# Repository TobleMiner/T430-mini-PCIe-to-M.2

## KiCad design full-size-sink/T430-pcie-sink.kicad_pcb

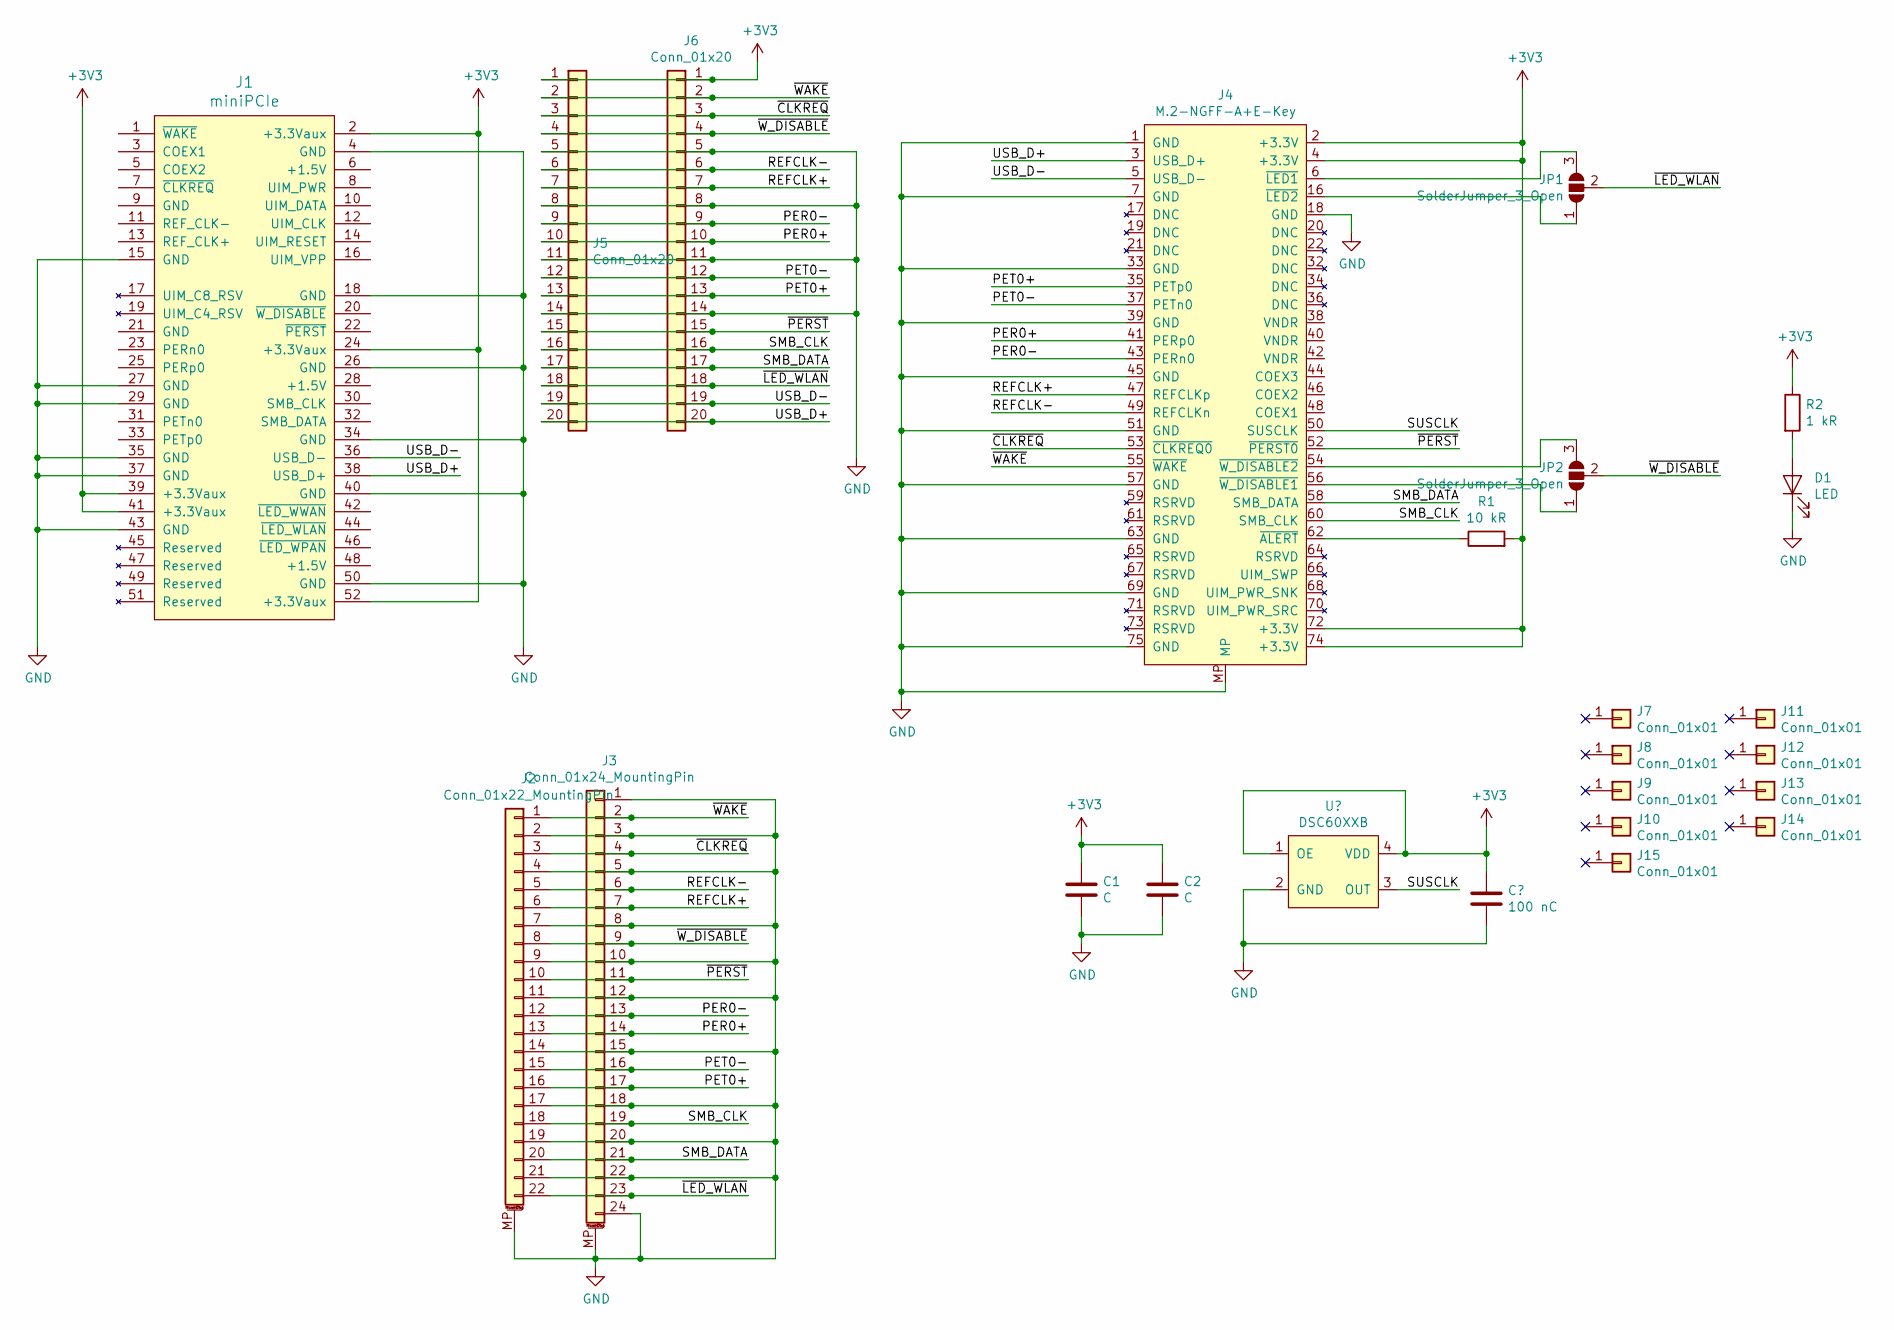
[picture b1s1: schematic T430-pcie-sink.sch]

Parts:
C1, C2: C; C_0805_2012Metric_Pad1.15x1.40mm_HandSolder
D1: LED; LED_0805_2012Metric_Castellated
J1: miniPCIe; mini-PCIe_F1_Full
J2: Conn_01x22_MountingPin; Molex-Easy-On-54548-2271-P0.5
J3: Conn_01x24_MountingPin; Molex-Easy-On-54548-2471-P0.5
J4: M.2-NGFF-A+E-Key; MDTXXXXXX001
J5: Conn_01x20; solder-20p-P1.0
J6: Conn_01x20; castellated-20p-P1.0
J7, J8, J9, J10, J11, J12, J13, J14: Conn_01x01; Pad-2.5x2.5
J15: Conn_01x01; screw-stud
JP1, JP2: SolderJumper_3_Open; SolderJumper-3_P1.3mm_Open_Pad1.0x1.5mm
R1: 10 kR; R_0805_2012Metric_Pad1.15x1.40mm_HandSolder
R2: 1 kR; R_0805_2012Metric_Pad1.15x1.40mm_HandSolder

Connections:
+3V3: C1.1, C2.1, J1.2 (+3.3Vaux), J1.24 (+3.3Vaux), J1.39 (+3.3Vaux), J1.41 (+3.3Vaux), J1.52 (+3.3Vaux), J4.2 (+3.3V), J4.4 (+3.3V), J4.72 (+3.3V), J4.74 (+3.3V), J5.1, J6.1, R1.2, R2.1; also elsewhere on the board
/PER0+: J2.13, J3.14, J4.41 (PERp0), J5.10, J6.10
/PER0-: J2.12, J3.13, J4.43 (PERn0), J5.9, J6.9
/PET0+: J2.16, J3.17, J4.35 (PETp0), J5.13, J6.13
/PET0-: J2.15, J3.16, J4.37 (PETn0), J5.12, J6.12
/REFCLK+: J2.6, J3.7, J4.47 (REFCLKp), J5.7, J6.7
/REFCLK-: J2.5, J3.6, J4.49 (REFCLKn), J5.6, J6.6
/SMB_CLK: J2.18, J3.19, J4.60 (SMB_CLK), J5.16, J6.16
/SMB_DATA: J2.20, J3.21, J4.58 (SMB_DATA), J5.17, J6.17
/SUSCLK: J4.50 (SUSCLK); also elsewhere on the board
/USB_D+: J1.38 (USB_D+), J4.3 (USB_D+), J5.20, J6.20
/USB_D-: J1.36 (USB_D-), J4.5 (USB_D-), J5.19, J6.19
/~CLKREQ: J2.3, J3.4, J4.53 (~CLKREQ0), J5.3, J6.3
/~LED_WLAN: J2.22, J3.23, J5.18, J6.18, JP1.2 (C)
/~PERST: J2.10, J3.11, J4.52 (~PERST0), J5.15, J6.15
/~WAKE: J2.1, J3.2, J4.55 (~WAKE), J5.2, J6.2
/~W_DISABLE: J2.8, J3.9, J5.4, J6.4, JP2.2 (C)
GND: C1.2, C2.2, D1.1 (K), J1.4 (GND), J1.15 (GND), J1.18 (GND), J1.26 (GND), J1.27 (GND), J1.29 (GND), J1.34 (GND), J1.35 (GND), J1.37 (GND), J1.40 (GND), J1.43 (GND), J1.50 (GND), J2.2, J2.4, J2.7, J2.9, J2.11, J2.14, J2.17, J2.19, J2.21, J2.MP (MountPin), J3.1, J3.3, J3.5, J3.8, J3.10, J3.12, J3.15, J3.18, J3.20, J3.22, J3.24, J3.MP (MountPin), J4.1 (GND), J4.7 (GND), J4.18 (GND), J4.33 (GND), J4.39 (GND), J4.45 (GND), J4.51 (GND), J4.57 (GND), J4.63 (GND), J4.69 (GND), J4.75 (GND), J4.MP, J5.5, J5.8, J5.11, J5.14, J6.5, J6.8, J6.11, J6.14; also elsewhere on the board
unnamed: D1.2 (A), R2.2
unnamed: J4.6 (~LED1), JP1.3 (B)
unnamed: J4.16 (~LED2), JP1.1 (A)
unnamed: J4.54 (~W_DISABLE2), JP2.3 (B)
unnamed: J4.56 (~W_DISABLE1), JP2.1 (A)
unnamed: J4.62 (~ALERT), R1.1

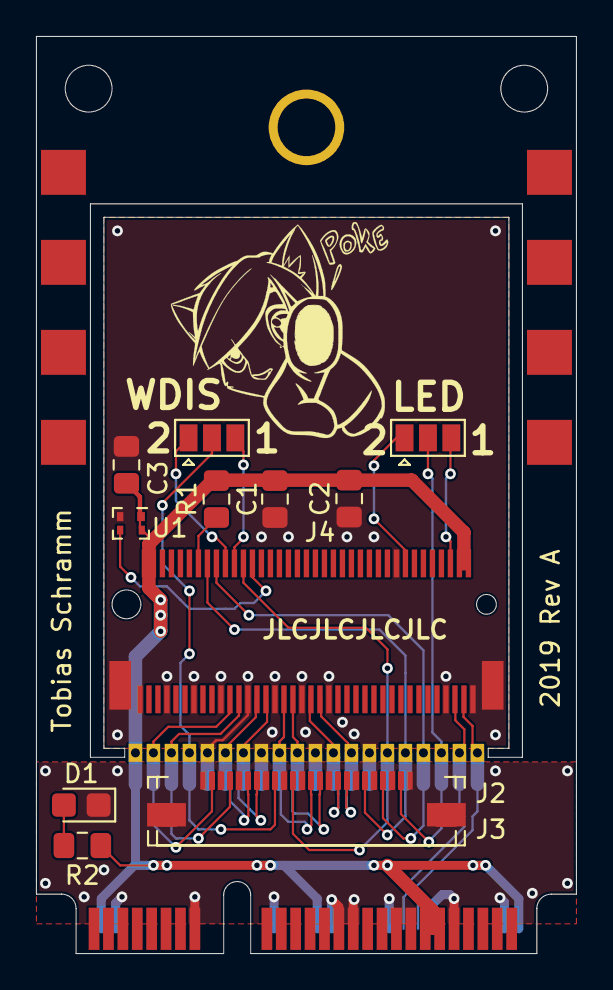
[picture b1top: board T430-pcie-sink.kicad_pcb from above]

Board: 2 copper layers, 30.0 x 51.0 mm, 24 parts (1 on the bottom side), 24 nets.

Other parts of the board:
C3: 100 nC; C_0805_2012Metric_Pad1.15x1.40mm_HandSolder
U1: DSC60XXB; LGA4-1.6x1.2

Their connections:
+3V3: C3.1, U1.1, U1.4; also elsewhere on the board
/SUSCLK: U1.3; also elsewhere on the board
GND: C3.2, U1.2; also elsewhere on the board

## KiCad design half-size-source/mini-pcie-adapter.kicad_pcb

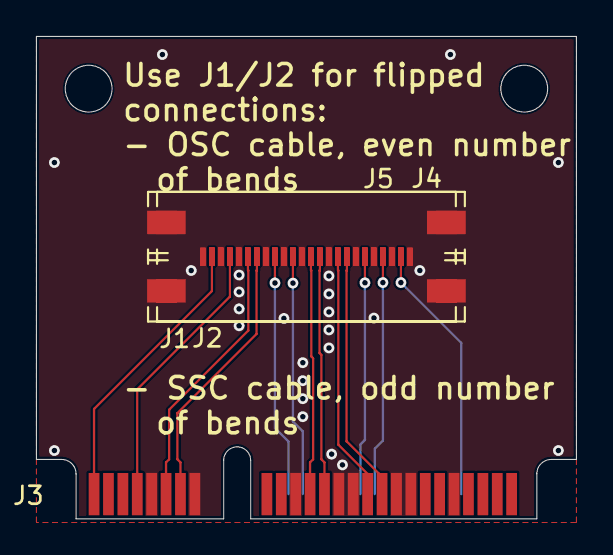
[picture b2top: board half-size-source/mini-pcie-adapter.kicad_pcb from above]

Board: 2 copper layers, 30.0 x 26.8 mm, 5 parts (0 on the bottom side), 14 nets.

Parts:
J1, J4: Conn_01x22_MountingPin; Molex-Easy-On-54548-2271-P0.5
J2, J5: Conn_01x24_MountingPin; Molex-Easy-On-54548-2471-P0.5
J3: miniPCIe; mini-PCIe_H1_Half

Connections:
/PER0+: J1.13, J2.14, J3.25, J4.10, J5.11
/PER0-: J1.12, J2.13, J3.23, J4.11, J5.12
/PET0+: J1.16, J2.17, J3.33, J4.7, J5.8
/PET0-: J1.15, J2.16, J3.31, J4.8, J5.9
/REF_CLK+: J1.6, J2.7, J3.13, J4.17, J5.18
/REF_CLK-: J1.5, J2.6, J3.11, J4.18, J5.19
/SMB_CLK: J1.18, J2.19, J3.30, J4.5, J5.6
/SMB_DATA: J1.20, J2.21, J3.32, J4.3, J5.4
/~CLKREQ: J1.3, J2.4, J3.7, J4.20, J5.21
/~LED_WLAN: J1.22, J2.23, J3.44, J4.1, J5.2
/~PERST: J1.10, J2.11, J3.22, J4.13, J5.14
/~WAKE: J1.1, J2.2, J3.1, J4.22, J5.23
/~W_DISABLE: J1.8, J2.9, J3.20, J4.15, J5.16
GND: J1.2, J1.4, J1.7, J1.9, J1.11, J1.14, J1.17, J1.19, J1.21, J1.MP, J2.1, J2.3, J2.5, J2.8, J2.10, J2.12, J2.15, J2.18, J2.20, J2.22, J2.24, J2.MP, J3.4, J3.9, J3.15, J3.18, J3.21, J3.26, J3.27, J3.29, J3.34, J3.35, J3.37, J3.40, J3.43, J3.50, J4.2, J4.4, J4.6, J4.9, J4.12, J4.14, J4.16, J4.19, J4.21, J4.MP, J5.1, J5.3, J5.5, J5.7, J5.10, J5.13, J5.15, J5.17, J5.20, J5.22, J5.24, J5.MP

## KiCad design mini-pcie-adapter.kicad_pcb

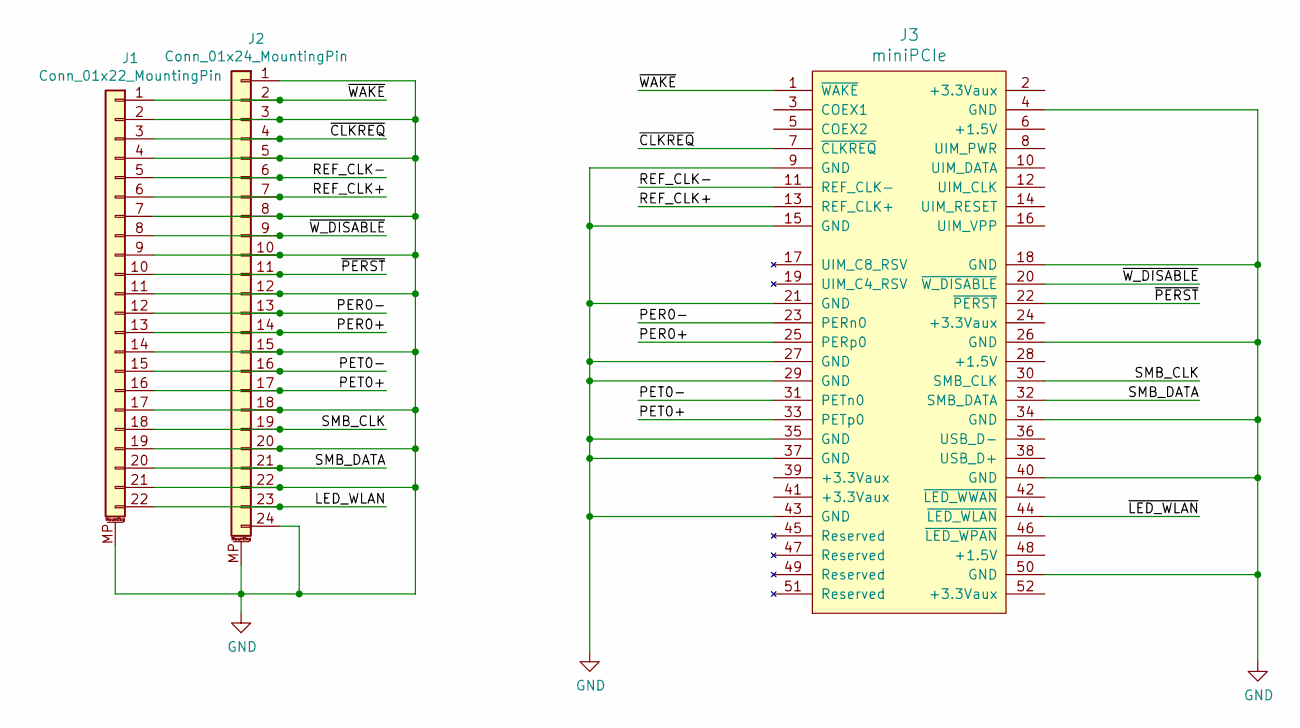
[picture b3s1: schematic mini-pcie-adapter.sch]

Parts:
J1: Conn_01x22_MountingPin; Molex-Easy-On-54548-2271-P0.5
J2: Conn_01x24_MountingPin; Molex-Easy-On-54548-2471-P0.5
J3: miniPCIe; mini-PCIe_H1_Half

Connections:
/LED_WLAN: J1.22, J2.23
/PER0+: J1.13, J2.14, J3.25 (PERp0)
/PER0-: J1.12, J2.13, J3.23 (PERn0)
/PET0+: J1.16, J2.17, J3.33 (PETp0)
/PET0-: J1.15, J2.16, J3.31 (PETn0)
/REF_CLK+: J1.6, J2.7, J3.13 (REF_CLK+)
/REF_CLK-: J1.5, J2.6, J3.11 (REF_CLK-)
/SMB_CLK: J1.18, J2.19, J3.30 (SMB_CLK)
/SMB_DATA: J1.20, J2.21, J3.32 (SMB_DATA)
/~CLKREQ: J1.3, J2.4, J3.7 (~CLKREQ)
/~LED_WLAN: J3.44 (~LED_WLAN)
/~PERST: J1.10, J2.11, J3.22 (~PERST)
/~WAKE: J1.1, J2.2, J3.1 (~WAKE)
/~W_DISABLE: J1.8, J2.9, J3.20 (~W_DISABLE)
GND: J1.2, J1.4, J1.7, J1.9, J1.11, J1.14, J1.17, J1.19, J1.21, J1.MP (MountPin), J2.1, J2.3, J2.5, J2.8, J2.10, J2.12, J2.15, J2.18, J2.20, J2.22, J2.24, J2.MP (MountPin), J3.4 (GND), J3.9 (GND), J3.15 (GND), J3.18 (GND), J3.21 (GND), J3.26 (GND), J3.27 (GND), J3.29 (GND), J3.34 (GND), J3.35 (GND), J3.37 (GND), J3.40 (GND), J3.43 (GND), J3.50 (GND)

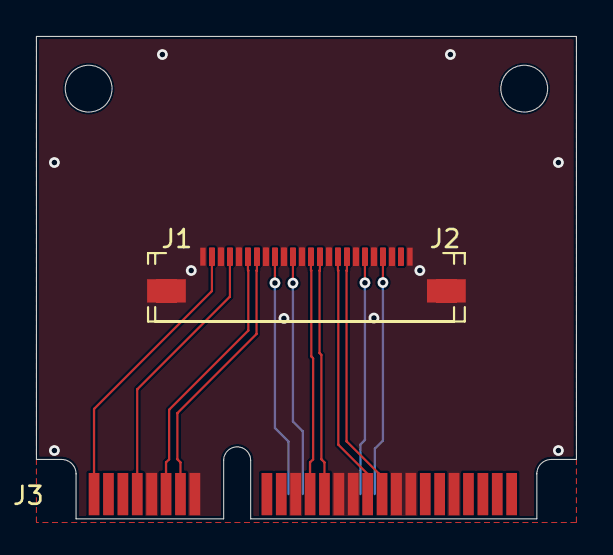
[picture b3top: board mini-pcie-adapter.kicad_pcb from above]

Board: 2 copper layers, 30.0 x 26.8 mm, 3 parts (0 on the bottom side), 14 nets.

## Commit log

2019-10-02 Add full-size FFC -> M.2 adapter
2019-10-02 De-skew PCIe lane 0 RX
2019-10-02 Move half-size adapter to separate project
2019-10-03 Add suspend oscillator
    Seems to be mandatory in the NGFF M.2 spec
